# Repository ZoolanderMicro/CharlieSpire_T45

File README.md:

# CharlieSpire_T45
  Sketch CharlieSpire_T45 is a routine for
  lighting a CharlieCube LED spire. Each
  spire uses 4 common-cathode RGB LEDs.
  The routine runs five different light
  patterns. Written for ATtiny45 (T45). 
  Sketch uses 3244 bytes (79%) of program
  storage space (Maximum is 4096 bytes).
  Global variables use 13 bytes
  (5% of dynamic memory). This code was 
  inspired by work done by Steve Yoshida (stevesprojectpages.com/) 
  I expanded upon his spire test code.
  Spire orientation of first LED (bottom)
  PIN_A is cathode, PIN_B is red LED,
  PIN_C is green LED, PIN_D is blue LED
  @author Mike Tonge (ZoolanderMicro)
  @date 11/28/2020

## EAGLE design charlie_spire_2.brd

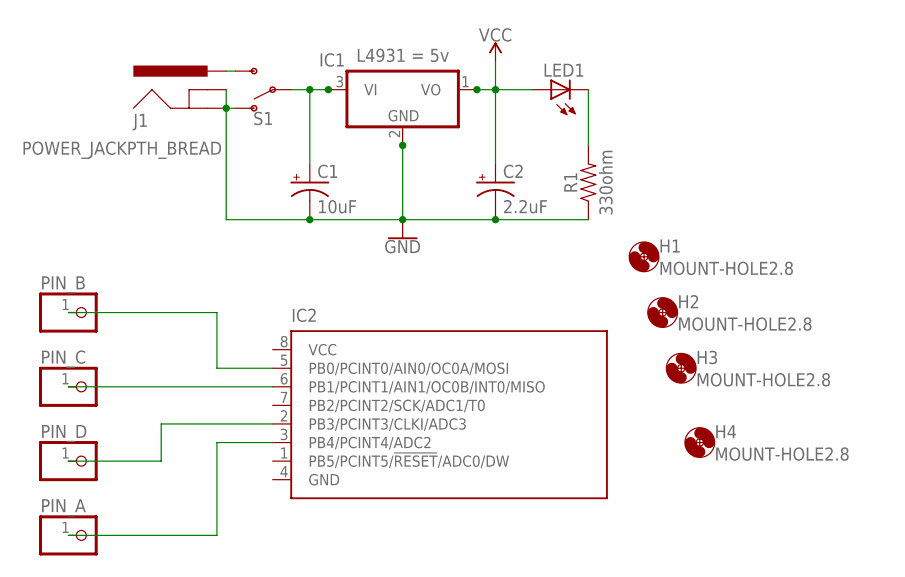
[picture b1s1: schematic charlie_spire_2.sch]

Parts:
C1: 10uF; CPOL-RADIAL-2.5MM-5MM
C2: 2.2uF; CPOL-RADIAL-2.5MM-5MM
H1, H2, H3, H4: MOUNT-HOLE2.8; 2,8
IC1: 78L05Z; TO92
IC2: TINY13V-10PU; DIL08; MPN ATTINY45
J1: POWER_JACKPTH_BREAD; POWER_JACK_PTH_BREAD
LED1: LED3MM
PIN_A: PINHD-1X1; 1X01
PIN_B: PINHD-1X1; 1X01
PIN_C: PINHD-1X1; 1X01
PIN_D: PINHD-1X1; 1X01
R1: 330ohm; AXIAL-0.3
S1: SWITCH-SPDT-PTH-11.6X4.0MM; SWITCH_SPDT_PTH_11.6X4.0MM

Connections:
GND: C1.2 (-), C2.2 (-), IC1.2 (GND), IC2.4 (GND), J1.GND, J1.GNDBREAK, R1.P$1 (1), S1.1 (O)
unnamed: J1.PWR, S1.3 (S)
unnamed: C1.1 (+), IC1.3 (VI), S1.2
unnamed: IC2.3 (PB4/PCINT4/ADC2), PIN_A.1
unnamed: LED1.K (C), R1.P$2 (2)
unnamed: IC2.5 (PB0/PCINT0/AIN0/OC0A/MOSI), PIN_B.1
unnamed: IC2.6 (PB1/PCINT1/AIN1/OC0B/INT0/MISO), PIN_C.1
unnamed: IC2.2 (PB3/PCINT3/CLKI/ADC3), PIN_D.1
VCC: C2.1 (+), IC1.1 (VO), IC2.8 (VCC), LED1.A

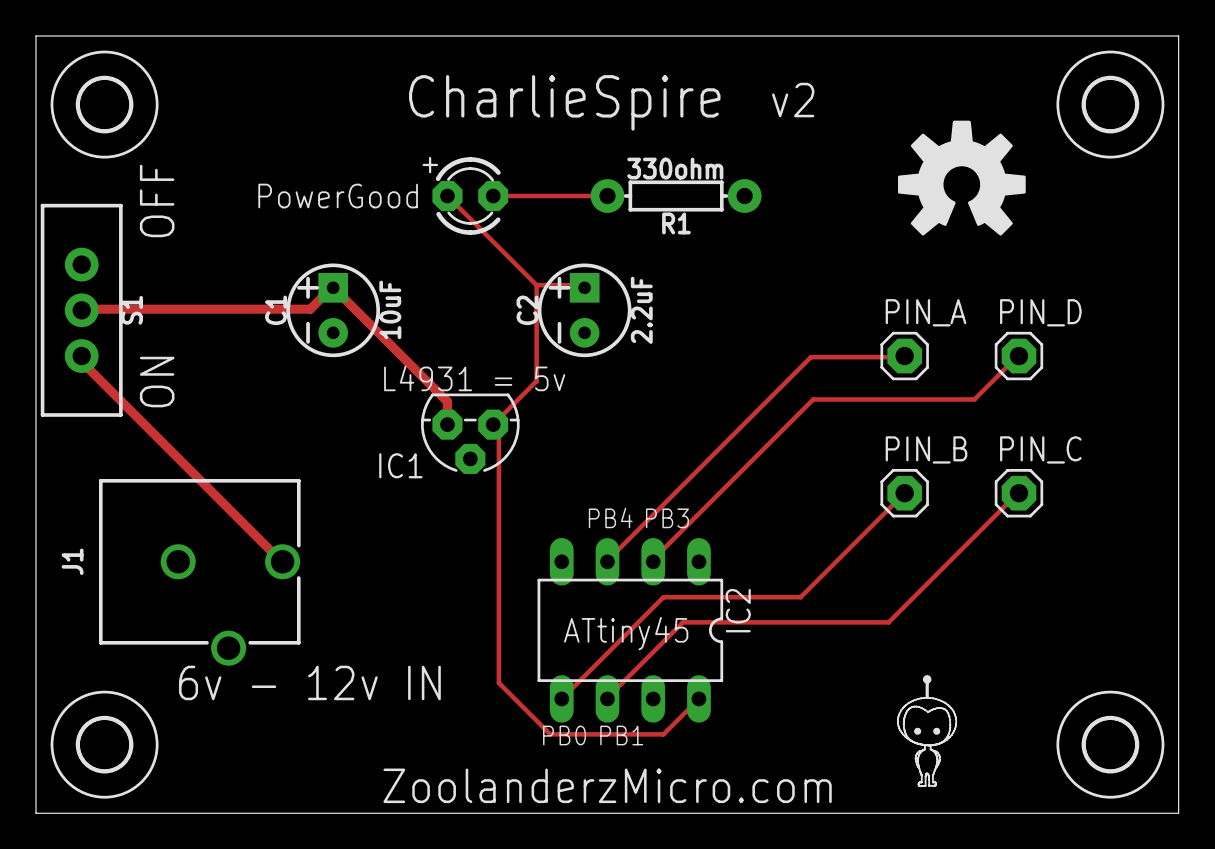
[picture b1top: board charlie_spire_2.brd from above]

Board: 2 copper layers, 63.5 x 43.2 mm, 18 parts (0 on the bottom side), 9 nets.

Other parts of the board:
U$1: OSHW-LOGO-L
U$2: QTECHKNOW-LOGO-SMALL-SILK

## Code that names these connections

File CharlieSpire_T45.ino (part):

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  @date 11/28/2020
*/
//------MAP--------Physical------IDE-----PORT
#define PIN_A 4 // T45 pin 3   (4/A2)    PB4
#define PIN_B 0 // T45 pin 5    (0)      PB0
#define PIN_C 1 // T45 pin 6    (1)      PB1
#define PIN_D 3 // T45 pin 2   (3/A3)    PB3

int longDelay = 40; // Long delay (miliseconds)
int shortDelay = 20; // Short delay (miliseconds)
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
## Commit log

2020-12-18 CharlieSpire board and schematic
    The CharlieSpire board and schematic files for the spire test board PCB.

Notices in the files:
parts and their libraries:
SparkFun-Capacitors: Licensing: Creative Commons ShareAlike 4.0 International - https://creativecommons.org/licenses/by-sa/4.0
